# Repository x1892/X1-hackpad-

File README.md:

# X1-hackpad-
Hi, I'm Riyad and this is my project.thanks a lot to Hardik and also thanks to hackpad
this is the base 
this is the pcb
here is the schematics
here is the top 
and the final view 
Bill of meterials
1.Xiao RP2040 - 1
2.Cherry MX switches - 4
3.Cherry MX keycaps - 4
4.Oled 0.91 - 1
5.Heat inserts and screws - 4

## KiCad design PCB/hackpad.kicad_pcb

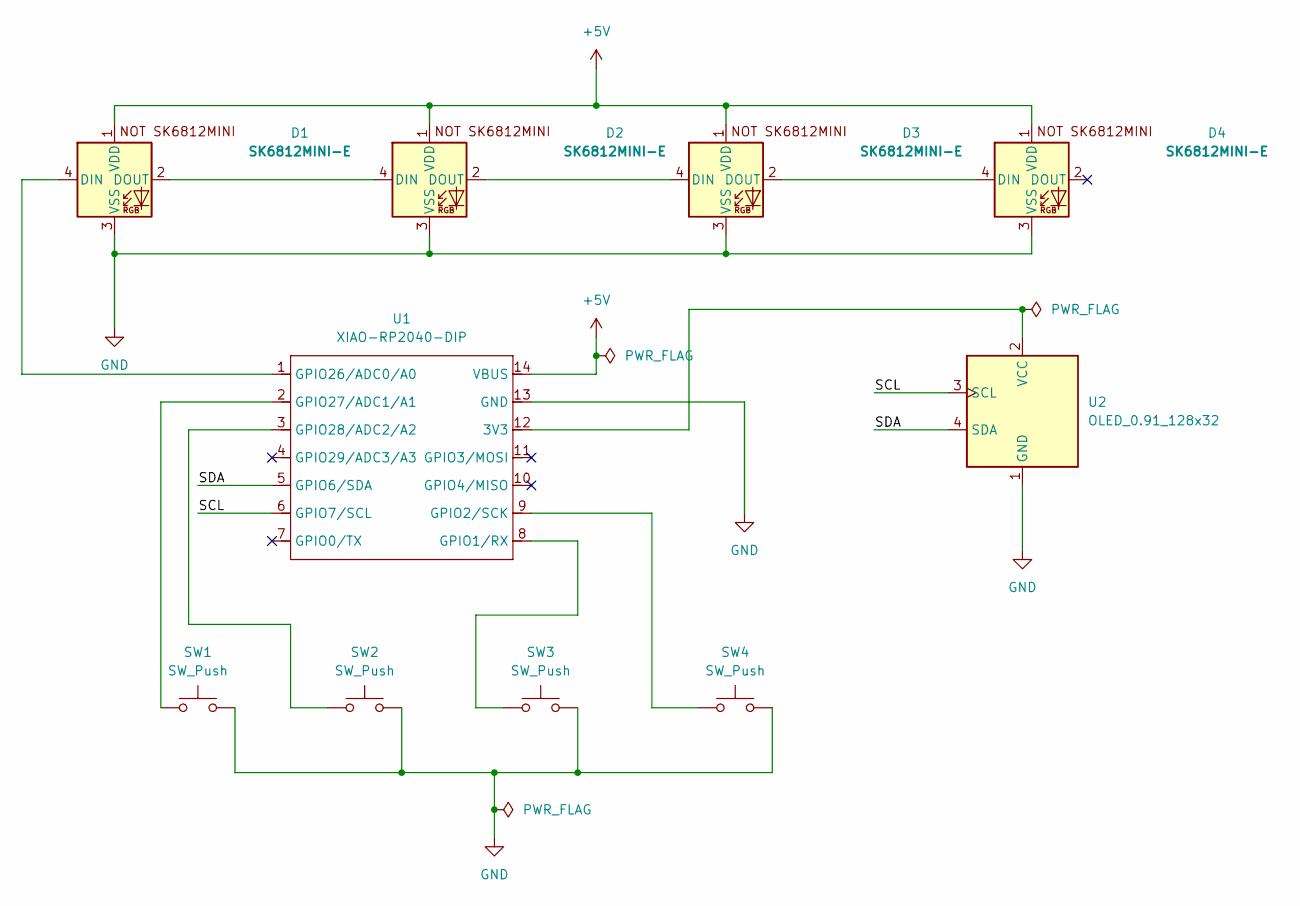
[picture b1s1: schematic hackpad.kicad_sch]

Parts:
D1, D2, D3, D4: SK6812MINI-E; MX_SK6812MINI-E_REV
SW1, SW2, SW3, SW4: SW_Push; SW_Cherry_MX_1.00u_PCB
U1: XIAO-RP2040-DIP
U2: OLED_0.91_128x32

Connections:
+5V: D1.1 (VDD), D2.1 (VDD), D3.1 (VDD), D4.1 (VDD), U1.14 (VBUS)
/SCL: U1.6 (GPIO7/SCL), U2.3 (SCL)
/SDA: U1.5 (GPIO6/SDA), U2.4 (SDA)
GND: D1.3 (VSS), D2.3 (VSS), D3.3 (VSS), D4.3 (VSS), SW1.2, SW2.2, SW3.2, SW4.2, U1.13 (GND), U2.1 (GND)
unnamed: D1.4 (DIN), U1.1 (GPIO26/ADC0/A0)
unnamed: D1.2 (DOUT), D2.4 (DIN)
unnamed: D2.2 (DOUT), D3.4 (DIN)
unnamed: D3.2 (DOUT), D4.4 (DIN)
unnamed: U1.12 (3V3), U2.2 (VCC)
unnamed: SW3.1, U1.8 (GPIO1/RX)
unnamed: SW4.1, U1.9 (GPIO2/SCK)
unnamed: SW1.1, U1.2 (GPIO27/ADC1/A1)
unnamed: SW2.1, U1.3 (GPIO28/ADC2/A2)

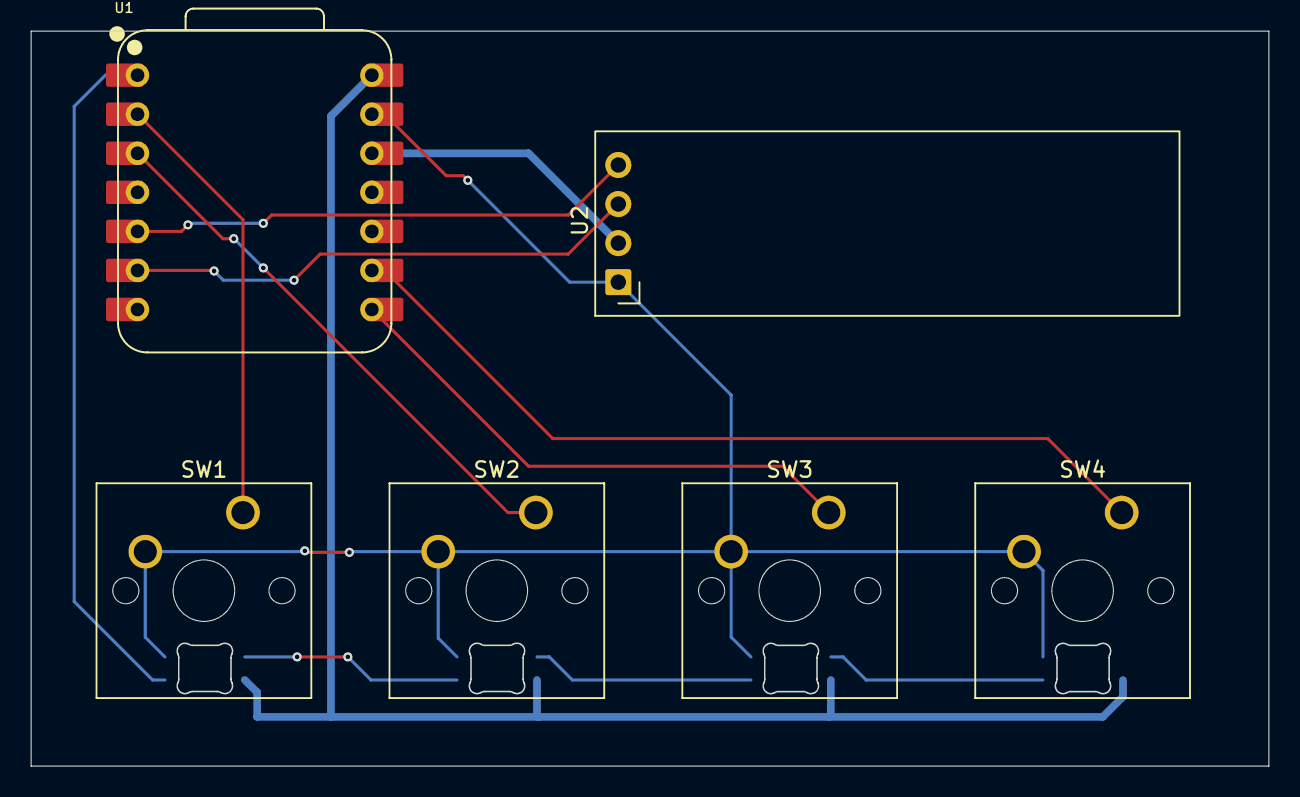
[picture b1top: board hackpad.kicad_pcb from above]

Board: 2 copper layers, 80.5 x 47.8 mm, 10 parts (0 on the bottom side), 13 nets.

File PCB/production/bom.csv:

Designator,Footprint,Quantity,Value,LCSC Part #
"D1, D2, D3, D4",MX_SK6812MINI-E_REV,4,SK6812MINI-E,
"SW1, SW2, SW3, SW4",SW_Cherry_MX_1.00u_PCB,4,SW_Push,
U1,XIAO-RP2040-DIP,1,XIAO-RP2040-DIP,
U2,OLED_0.91_128x32,1,OLED_0.91_128x32,

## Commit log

2026-01-04 Add project images to README
    Added images of the project components including the base, PCB, schematics, top view, and final assembled view.
2026-01-04 Add Bill of Materials to README
    Added a Bill of Materials section with component details.
2026-01-04 Number the items in the bill of materials
    Updated the bill of materials to include numbering.
